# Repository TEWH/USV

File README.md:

Ultrasonic Vision for th Visually Impaired

At least 2.2 billion people worldwide suffer from blindness or visual impairment.1 These conditions are estimated to be four times more prevalent for low and middle income regions and the most prevalent in developing countries where conditions such as malnutrition, lack of sanitation, and inadequate health services result in a high incidence of eye disease.2 Visual impairment and blindness can be detrimental in developing countries that lack resources to integrate blind members into society. Some previous efforts to reduce the occurrence of blindness in third world countries include preventative screening programs like the eye-care services assessment tool implemented by the World Health Organization. Additionally, blindness caused by cataracts can be treated through ophthalmic surgeries, and several organizations like the Himalayan Cataract Project have corrected cataracts in over 800,000 people.3 However, fewer measures have been taken to provide wide-spread support for those who are either untreatable with cataract surgery, have chronic visual impairment, or those who are waiting to receive surgery. With our device, we aim to design a cost-effective, easy to use method for blind and visually impaired people to be able to detect the location of nearby objects. We are developing a haptic-feedback navigational system that utilizes ultrasonic sensors and a Bluetooth system.

Our device is an affordable system that consists of a belt and glasses for the detection of objects within approximately 2 m to the lower body and upper body respectively. In an effort to improve the existing condition of blindness in developing communities, our system can be used in all environments without requiring connectivity to a Wi-Fi network. As it is powered by simple batteries, it requires minimal repairs and updates, and it can be worn by virtually anyone due to its adjustable features.

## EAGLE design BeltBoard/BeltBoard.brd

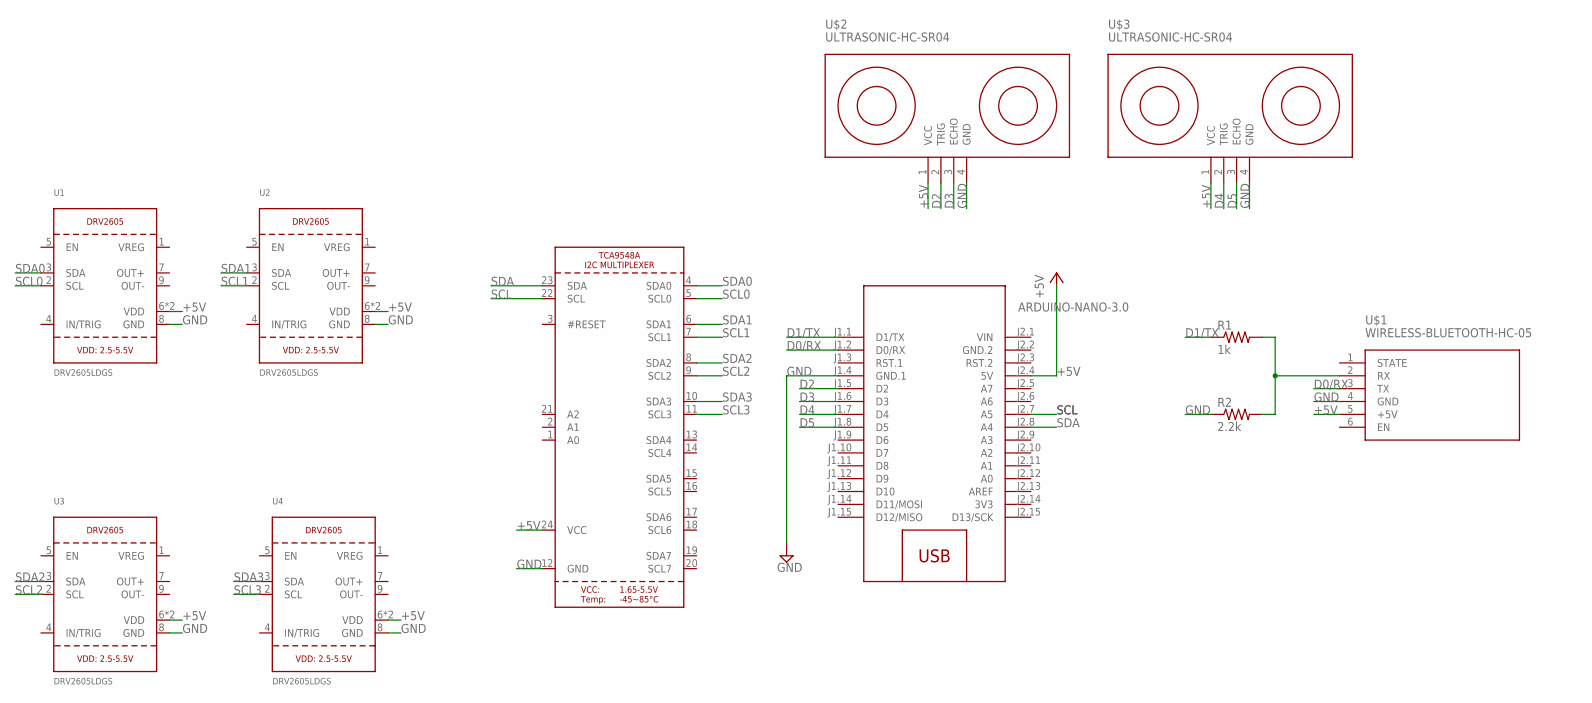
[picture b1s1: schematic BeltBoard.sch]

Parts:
M1: ARDUINO-NANO-3.0
R1: 1k; R0805
R2: 2.2k; R0805
U1, U2, U3, U4: DRV2605LDGS; PSOP10
U5: TCA9548APWR; TSSOP24
U$1: WIRELESS-BLUETOOTH-HC-05
U$2, U$3: ULTRASONIC-HC-SR04

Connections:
3V3: M1.J2.14 (3V3)
+5V: M1.J2.4 (5V), U1.6 (VDD), U1.10 (VDD), U2.6 (VDD), U2.10 (VDD), U3.6 (VDD), U3.10 (VDD), U4.6 (VDD), U4.10 (VDD), U5.24 (VCC), U$1.5 (+5V), U$2.1 (VCC), U$3.1 (VCC)
D0/RX: M1.J1.2 (D0/RX), U$1.3 (TX)
D1/TX: M1.J1.1 (D1/TX), R1.1
D2: M1.J1.5 (D2), U$2.2 (TRIG)
D3: M1.J1.6 (D3), U$2.3 (ECHO)
D4: M1.J1.7 (D4), U$3.2 (TRIG)
D5: M1.J1.8 (D5), U$3.3 (ECHO)
GND: M1.J1.4 (GND.1), R2.1, U1.8 (GND), U2.8 (GND), U3.8 (GND), U4.8 (GND), U5.12 (GND), U$1.4 (GND), U$2.4 (GND), U$3.4 (GND)
GND.2: M1.J2.2 (GND.2)
unnamed: R1.2, R2.2, U$1.2 (RX)
SCL: M1.J2.7 (A5), U5.22 (SCL)
SCL0: U1.2 (SCL), U5.5 (SCL0)
SCL1: U2.2 (SCL), U5.7 (SCL1)
SCL2: U3.2 (SCL), U5.9 (SCL2)
SCL3: U4.2 (SCL), U5.11 (SCL3)
SDA: M1.J2.8 (A4), U5.23 (SDA)
SDA0: U1.3 (SDA), U5.4 (SDA0)
SDA1: U2.3 (SDA), U5.6 (SDA1)
SDA2: U3.3 (SDA), U5.8 (SDA2)
SDA3: U4.3 (SDA), U5.10 (SDA3)
VIN: M1.J2.1 (VIN)

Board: 2 copper layers, 11 parts (0 on the bottom side), 19 nets, no tracks yet.

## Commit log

2020-02-23 Adding belt and goggles
2020-03-01 Adding Belt Board
2020-04-09 Rename Belt.ino to BeltMk2.ino
2020-04-09 Rename BeltMk2.ino to Belt.ino
2020-05-30 Organized repo

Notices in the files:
parts and their libraries:
diy-modules: Released under the Creative Commons Attribution 4.0 International License: http://creativecommons.org/licenses/by/4.0
microbuilder: This work is placed in the public domain, and may be freely used for commercial and non-commercial work with the following conditions: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
